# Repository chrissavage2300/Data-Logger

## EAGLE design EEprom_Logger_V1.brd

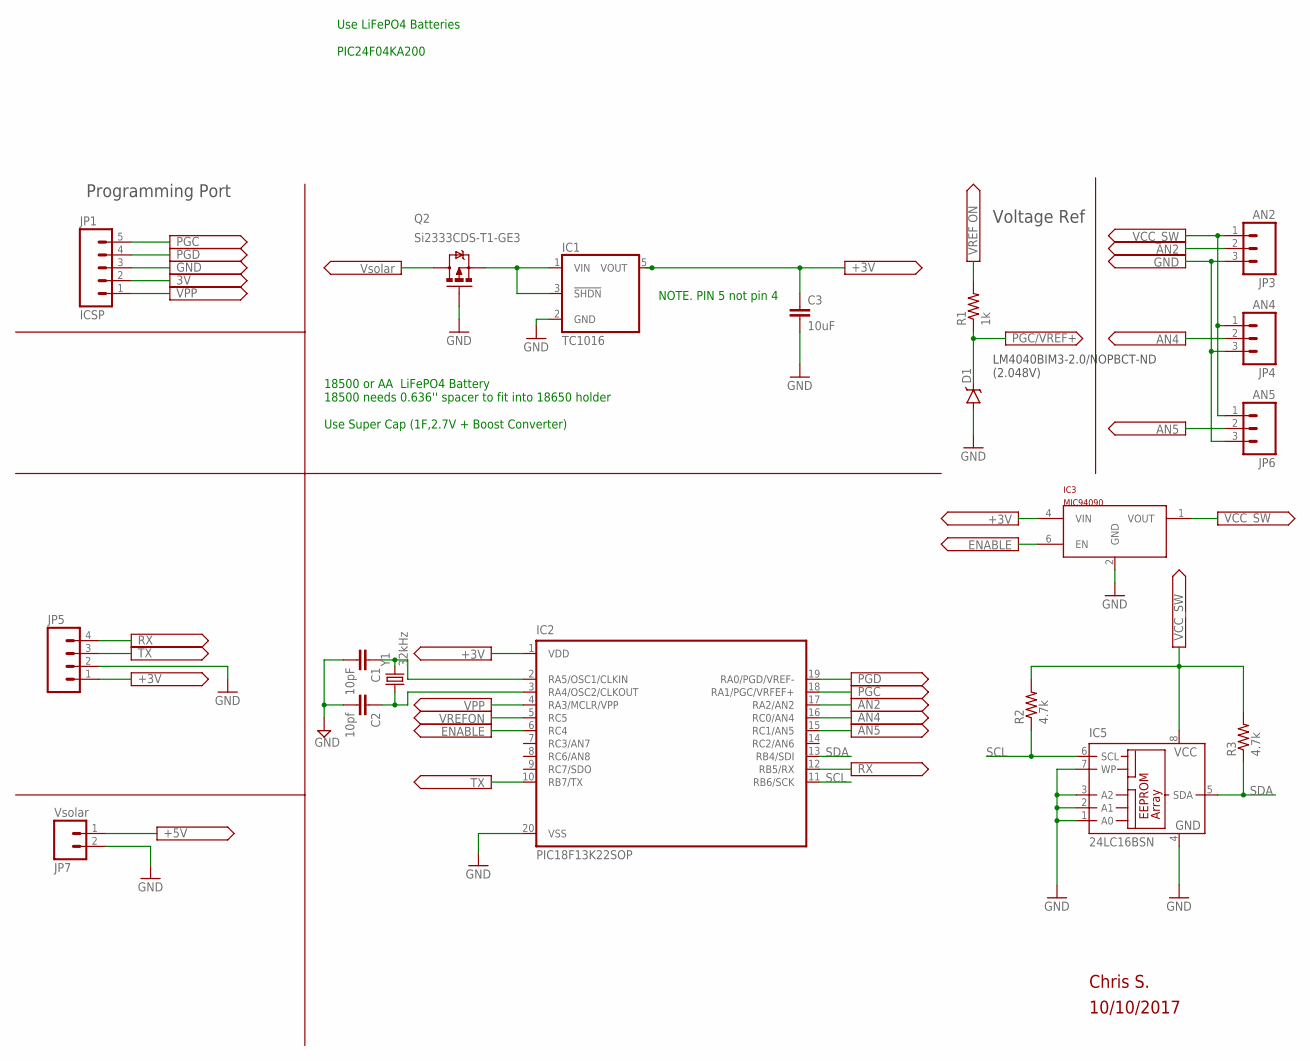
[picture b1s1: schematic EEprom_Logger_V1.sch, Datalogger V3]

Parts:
C1: 10pF; 1206
C2: 10pf; 1206
C3: 10uF; 1206
D1: V-REFERENCESMD; SOT23-3
IC1: TC1016; SOT23-5L
IC2: PIC18F13K22SOP; SOP20W
IC3: MIC94090; SC-70
IC5: 24LC16BSN; SO-08
JP1: ICSP; 1X05
JP3: AN2; JST-3-PTH
JP4: AN4; JST-3-PTH
JP5: M04PTH; 1X04
JP6: AN5; JST-3-PTH
JP7: Vsolar; JST-2-PTH
Q2: Si2333CDS-T1-GE3; SOT23-3
R1: 1k; 1206
R2, R3: 4.7k; 1206
Y1: 32kHz; TC26V

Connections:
3V: C3.1, IC1.5 (VOUT), IC2.1 (VDD), IC3.4 (VIN), JP1.2, JP5.1
AN2: IC2.17 (RA2/AN2), JP3.2
AN4: IC2.16 (RC0/AN4), JP4.2
AN5: IC2.15 (RC1/AN5), JP6.2
ENABLE: IC2.6 (RC4), IC3.6 (EN)
GND: C1.2, C2.2, C3.2, D1.2 (A), IC1.2 (GND), IC2.20 (VSS), IC3.2 (GND), IC5.1 (A0), IC5.2 (A1), IC5.3 (A2), IC5.4 (GND), IC5.7 (WP), JP1.3, JP3.3, JP4.3, JP5.2, JP6.3, JP7.2, Q2.1 (G)
unnamed: C1.1, IC2.2 (RA5/OSC1/CLKIN), Y1.2
unnamed: C2.1, IC2.3 (RA4/OSC2/CLKOUT), Y1.1
PGC: D1.1 (C), IC2.18 (RA1/PGC/VRFEF+), JP1.5, R1.1
PGD: IC2.19 (RA0/PGD/VREF-), JP1.4
RX: IC2.12 (RB5/RX), JP5.4
SCL: IC2.11 (RB6/SCK), IC5.6 (SCL), R2.1
SDA: IC2.13 (RB4/SDI), IC5.5 (SDA), R3.1
SWITCHED_VCC: IC3.1 (VOUT), IC5.8 (VCC), JP3.1, JP4.1, JP6.1, R2.2, R3.2
TX: IC2.10 (RB7/TX), JP5.3
VIN: IC1.1 (VIN), IC1.3 (!SHDN), Q2.2 (S)
VPP: IC2.4 (RA3/MCLR/VPP), JP1.1
VREFON: IC2.5 (RC5), R1.2
VSOLAR: JP7.1, Q2.3 (D)

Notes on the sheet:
LM4040BIM3-2.0/NOPBCT-ND (2.048V)
Voltage Ref
Chris S.
10/10/2017
Programming Port
NOTE. PIN 5 not pin 4
Use LiFePO4 Batteries PIC24F04KA200
18500 or AA LiFePO4 Battery 18500 needs 0.636'' spacer to fit into 18650 holder Use Super Cap (1F,2.7V + Boost Converter)

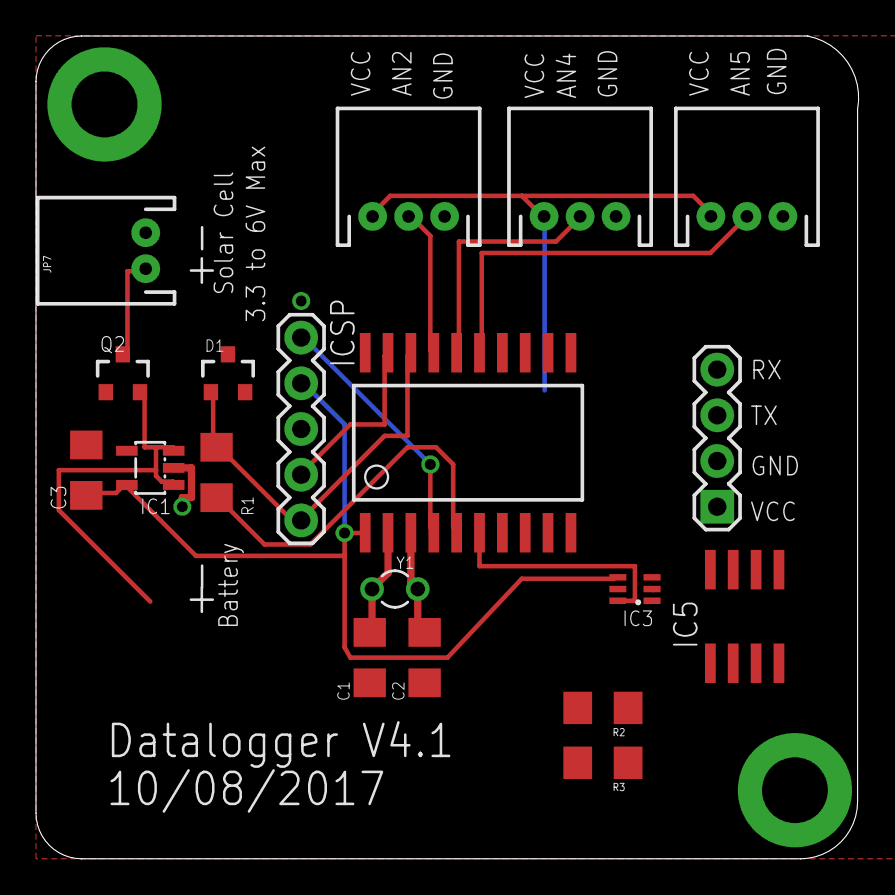
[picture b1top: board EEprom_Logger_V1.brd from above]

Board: 2 copper layers, 45.7 x 45.7 mm, 19 parts (0 on the bottom side), 19 nets.

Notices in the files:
parts and their libraries:
SparkFun-Connectors: Licensing: Creative Commons ShareAlike 4.0 International - https://creativecommons.org/licenses/by-sa/4.0
